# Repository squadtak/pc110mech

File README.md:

# pc110mech
IBM PalmTop PC110 Mechanical design

# ALL DESIGN ARE NOT TESTED/CHECKED.

## [pc110](/pc110)
reverse engeneered pc110 mechanical design. in progress.....

## [molex52960orig](/molex52960orig)
reverse engeneered Molex 52960 (replicator side) port expansion connector.

## [molex53711orig](/molex53711orig)
reverse engeneered Molex 53711 (pc110 side) port expansion connector.

## [molex52960FX6](/molex52960FX6)
redesigned Molex 52960 (replicator side) port expansion connector.

with Hirose FX6 connector.

## [molex53711FX6](/molex53711FX6)
redesigned Molex 53711 (pc110 side) port expansion connector.

with Hirose FX6 connector.

## [hosidenTCX5108-0111177](/hosidenTCX5108-0111177)
reverse engeneered Hosiden TCX5108-0111177 connector.

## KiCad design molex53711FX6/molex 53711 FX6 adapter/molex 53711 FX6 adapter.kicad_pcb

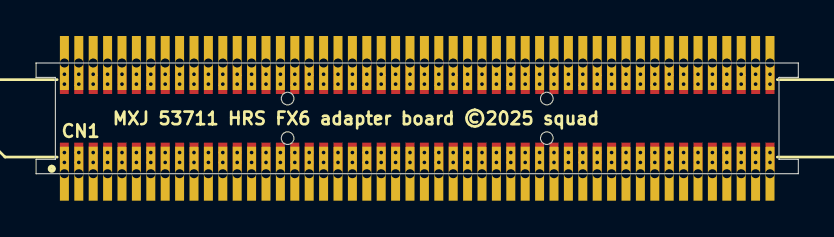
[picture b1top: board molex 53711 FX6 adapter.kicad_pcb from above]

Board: 2 copper layers, 42.4 x 6.2 mm, 101 parts (0 on the bottom side), 100 nets.

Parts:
CN1: FX6A-100P-0.8SVx(xx)
PAD1, PAD2, PAD3, PAD4, PAD5, PAD6, PAD7, PAD8, PAD9, PAD10, PAD11, PAD12, PAD13, PAD14, PAD15, PAD16, PAD17, PAD18, PAD19, PAD20, PAD21, PAD22, PAD23, PAD24, PAD25, PAD26, PAD27, PAD28, PAD29, PAD30, PAD31, PAD32, PAD33, PAD34, PAD35, PAD36, PAD37, PAD38, PAD39, PAD40, PAD41, PAD42, PAD43, PAD44, PAD45, PAD46, PAD47, PAD48, PAD49, PAD50, PAD51, PAD52, PAD53, PAD54, PAD55, PAD56, PAD57, PAD58, PAD59, PAD60, PAD61, PAD62, PAD63, PAD64, PAD65, PAD66, PAD67, PAD68, PAD69, PAD70, PAD71, PAD72, PAD73, PAD74, PAD75, PAD76, PAD77, PAD78, PAD79, PAD80, PAD81, PAD82, PAD83, PAD84, PAD85, PAD86, PAD87, PAD88, PAD89, PAD90, PAD91, PAD92, PAD93, PAD94, PAD95, PAD96, PAD97, PAD98, PAD99, PAD100: TH-0.5MM

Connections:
unnamed: CN1.1, PAD1.1
unnamed: CN1.2, PAD2.1
unnamed: CN1.3, PAD3.1
unnamed: CN1.4, PAD4.1
unnamed: CN1.5, PAD5.1
unnamed: CN1.6, PAD6.1
unnamed: CN1.7, PAD7.1
unnamed: CN1.8, PAD8.1
unnamed: CN1.9, PAD9.1
unnamed: CN1.10, PAD10.1
unnamed: CN1.11, PAD11.1
unnamed: CN1.12, PAD12.1
unnamed: CN1.13, PAD13.1
unnamed: CN1.14, PAD14.1
unnamed: CN1.15, PAD15.1
unnamed: CN1.16, PAD16.1
unnamed: CN1.17, PAD17.1
unnamed: CN1.18, PAD18.1
unnamed: CN1.19, PAD19.1
unnamed: CN1.20, PAD20.1
unnamed: CN1.21, PAD21.1
unnamed: CN1.22, PAD22.1
unnamed: CN1.23, PAD23.1
unnamed: CN1.24, PAD24.1
unnamed: CN1.25, PAD25.1
unnamed: CN1.26, PAD26.1
unnamed: CN1.27, PAD27.1
unnamed: CN1.28, PAD28.1
unnamed: CN1.29, PAD29.1
unnamed: CN1.30, PAD30.1
unnamed: CN1.31, PAD31.1
unnamed: CN1.32, PAD32.1
unnamed: CN1.33, PAD33.1
unnamed: CN1.34, PAD34.1
unnamed: CN1.35, PAD35.1
unnamed: CN1.36, PAD36.1
unnamed: CN1.37, PAD37.1
unnamed: CN1.38, PAD38.1
unnamed: CN1.39, PAD39.1
unnamed: CN1.40, PAD40.1
unnamed: CN1.41, PAD41.1
unnamed: CN1.42, PAD42.1
unnamed: CN1.43, PAD43.1
unnamed: CN1.44, PAD44.1
unnamed: CN1.45, PAD45.1
unnamed: CN1.46, PAD46.1
unnamed: CN1.47, PAD47.1
unnamed: CN1.48, PAD48.1
unnamed: CN1.49, PAD49.1
unnamed: CN1.50, PAD50.1
unnamed: CN1.51, PAD51.1
unnamed: CN1.52, PAD52.1
unnamed: CN1.53, PAD53.1
unnamed: CN1.54, PAD54.1
unnamed: CN1.55, PAD55.1
unnamed: CN1.56, PAD56.1
unnamed: CN1.57, PAD57.1
unnamed: CN1.58, PAD58.1
unnamed: CN1.59, PAD59.1
unnamed: CN1.60, PAD60.1
unnamed: CN1.61, PAD61.1
unnamed: CN1.62, PAD62.1
unnamed: CN1.63, PAD63.1
unnamed: CN1.64, PAD64.1
unnamed: CN1.65, PAD65.1
unnamed: CN1.66, PAD66.1
unnamed: CN1.67, PAD67.1
unnamed: CN1.68, PAD68.1
unnamed: CN1.69, PAD69.1
unnamed: CN1.70, PAD70.1
unnamed: CN1.71, PAD71.1
unnamed: CN1.72, PAD72.1
unnamed: CN1.73, PAD73.1
unnamed: CN1.74, PAD74.1
unnamed: CN1.75, PAD75.1
unnamed: CN1.76, PAD76.1
unnamed: CN1.77, PAD77.1
unnamed: CN1.78, PAD78.1
unnamed: CN1.79, PAD79.1
unnamed: CN1.80, PAD80.1
unnamed: CN1.81, PAD81.1
unnamed: CN1.82, PAD82.1
unnamed: CN1.83, PAD83.1
unnamed: CN1.84, PAD84.1
unnamed: CN1.85, PAD85.1
unnamed: CN1.86, PAD86.1
unnamed: CN1.87, PAD87.1
unnamed: CN1.88, PAD88.1
unnamed: CN1.89, PAD89.1
unnamed: CN1.90, PAD90.1
unnamed: CN1.91, PAD91.1
unnamed: CN1.92, PAD92.1
unnamed: CN1.93, PAD93.1
unnamed: CN1.94, PAD94.1
unnamed: CN1.95, PAD95.1
unnamed: CN1.96, PAD96.1
unnamed: CN1.97, PAD97.1
unnamed: CN1.98, PAD98.1
unnamed: CN1.99, PAD99.1
unnamed: CN1.100, PAD100.1

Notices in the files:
molex53711FX6/molex 53711 FX6 adapter/molex 53711 FX6 adapter.kicad_pcb:
MXJ 53711 HRS FX6 adapter board ©2025 squad
